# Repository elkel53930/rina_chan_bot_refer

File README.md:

**3DCADデータはこちら https://a360.co/3BOVUqo**

このリポジトリは璃奈ちゃんbotのコードの一部を参考のために公開するものです。

これらのコードは十分に整理されたものではありません。
また、あくまで参考のためのコードで、動作に必要なコードが全て揃っている保証もありません。

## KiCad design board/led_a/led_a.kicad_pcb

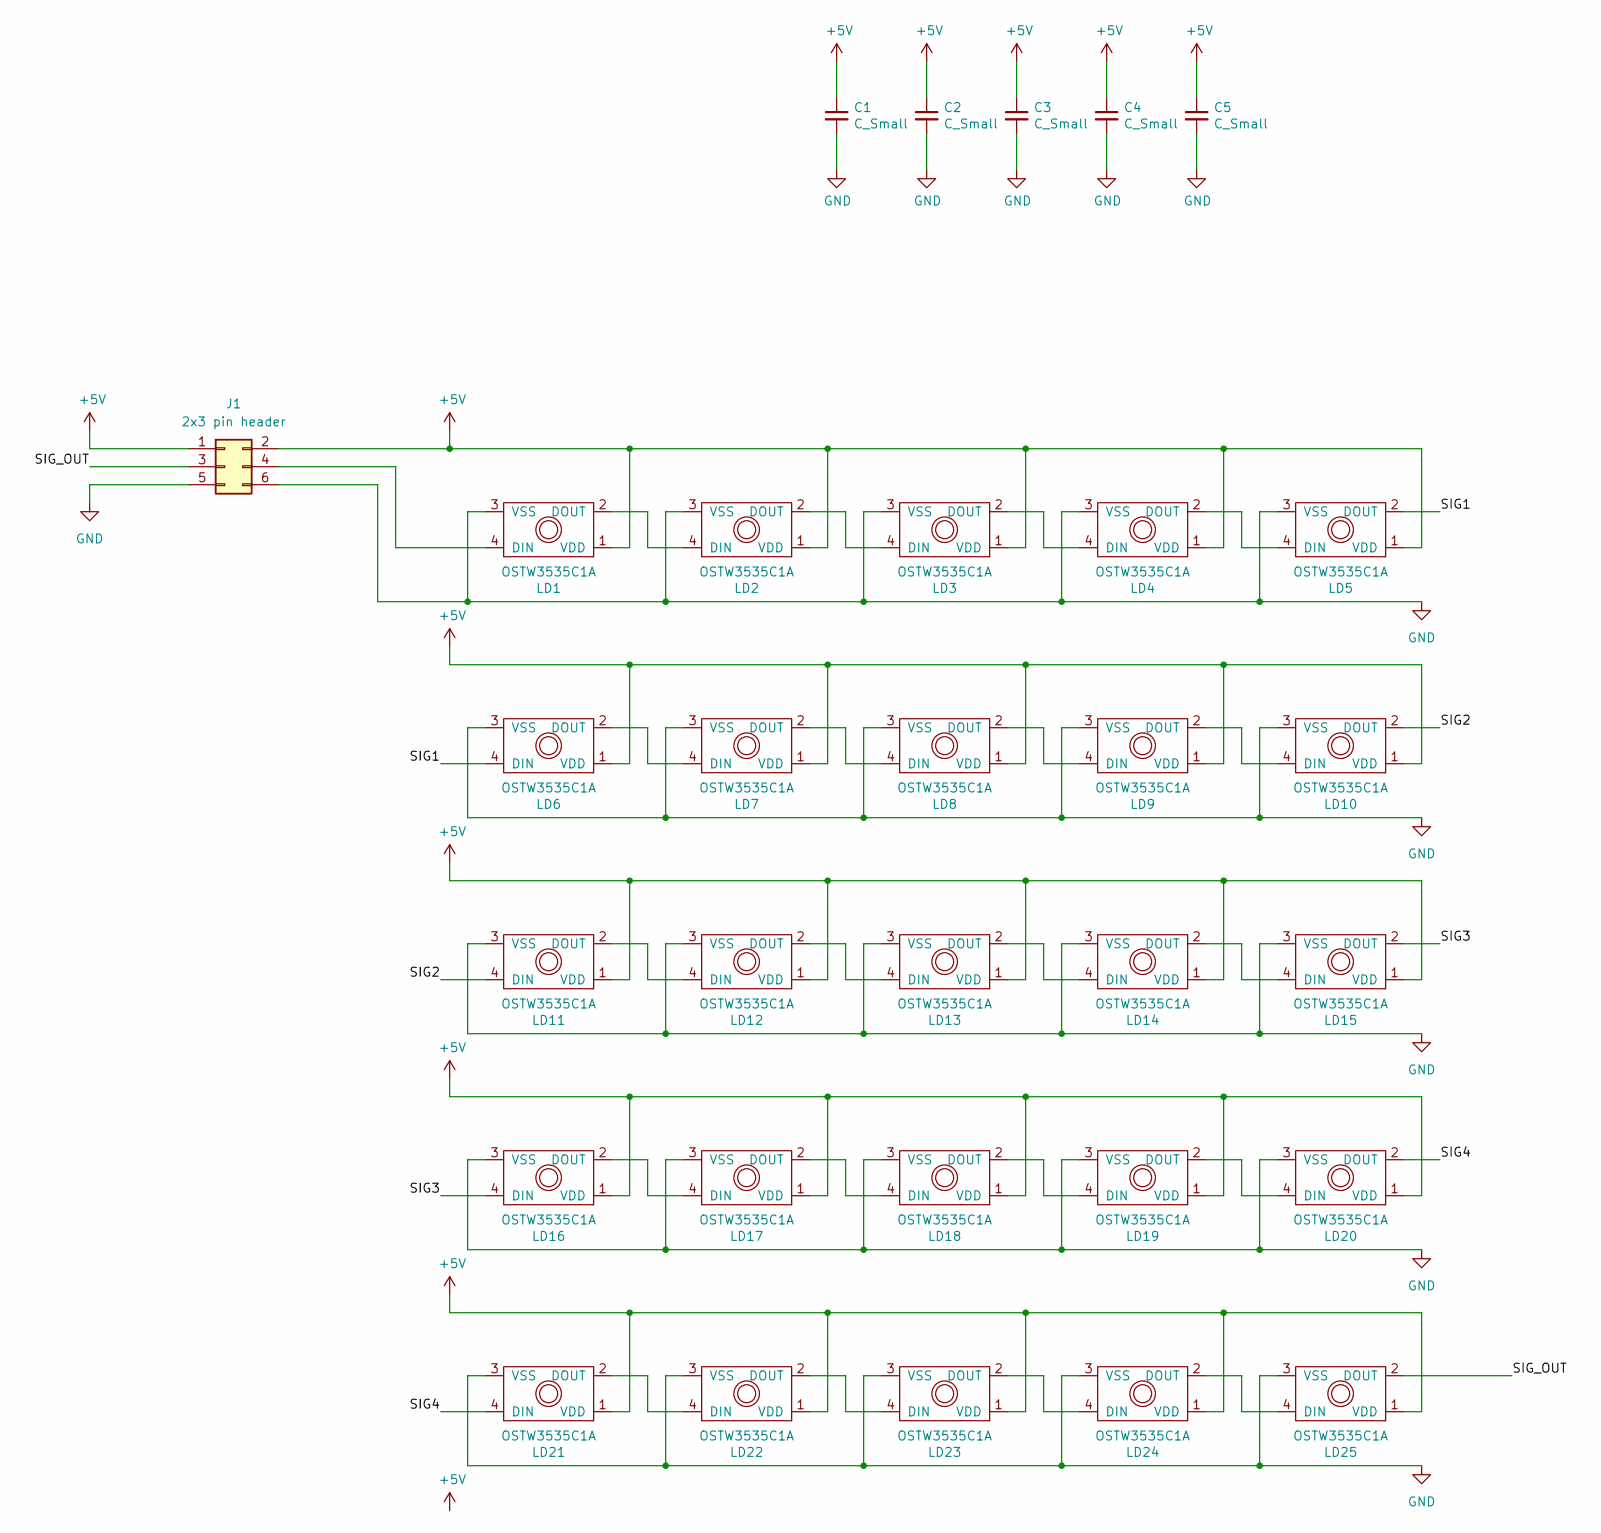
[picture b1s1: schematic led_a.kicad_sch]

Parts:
C1, C2, C3, C4, C5: C_Small; C_1206_3216Metric_Pad1.33x1.80mm_HandSolder
J1: 2x3 pin header; PinHeader_2x03_P2.54mm_Vertical
LD1, LD2, LD3, LD4, LD5, LD6, LD7, LD8, LD9, LD10, LD11, LD12, LD13, LD14, LD15, LD16, LD17, LD18, LD19, LD20, LD21, LD22, LD23, LD24, LD25: OSTW3535C1A

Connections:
+5V: C1.1, C2.1, C3.1, C4.1, C5.1, J1.1, J1.2, LD1.1 (VDD), LD2.1 (VDD), LD3.1 (VDD), LD4.1 (VDD), LD5.1 (VDD), LD6.1 (VDD), LD7.1 (VDD), LD8.1 (VDD), LD9.1 (VDD), LD10.1 (VDD), LD11.1 (VDD), LD12.1 (VDD), LD13.1 (VDD), LD14.1 (VDD), LD15.1 (VDD), LD16.1 (VDD), LD17.1 (VDD), LD18.1 (VDD), LD19.1 (VDD), LD20.1 (VDD), LD21.1 (VDD), LD22.1 (VDD), LD23.1 (VDD), LD24.1 (VDD), LD25.1 (VDD)
/SIG1: LD5.2 (DOUT), LD6.4 (DIN)
/SIG2: LD10.2 (DOUT), LD11.4 (DIN)
/SIG3: LD15.2 (DOUT), LD16.4 (DIN)
/SIG4: LD20.2 (DOUT), LD21.4 (DIN)
/SIG_OUT: J1.3, LD25.2 (DOUT)
GND: C1.2, C2.2, C3.2, C4.2, C5.2, J1.5, J1.6, LD1.3 (VSS), LD2.3 (VSS), LD3.3 (VSS), LD4.3 (VSS), LD5.3 (VSS), LD6.3 (VSS), LD7.3 (VSS), LD8.3 (VSS), LD9.3 (VSS), LD10.3 (VSS), LD11.3 (VSS), LD12.3 (VSS), LD13.3 (VSS), LD14.3 (VSS), LD15.3 (VSS), LD16.3 (VSS), LD17.3 (VSS), LD18.3 (VSS), LD19.3 (VSS), LD20.3 (VSS), LD21.3 (VSS), LD22.3 (VSS), LD23.3 (VSS), LD24.3 (VSS), LD25.3 (VSS)
unnamed: LD1.2 (DOUT), LD2.4 (DIN)
unnamed: J1.4, LD1.4 (DIN)
unnamed: LD2.2 (DOUT), LD3.4 (DIN)
unnamed: LD3.2 (DOUT), LD4.4 (DIN)
unnamed: LD4.2 (DOUT), LD5.4 (DIN)
unnamed: LD6.2 (DOUT), LD7.4 (DIN)
unnamed: LD7.2 (DOUT), LD8.4 (DIN)
unnamed: LD8.2 (DOUT), LD9.4 (DIN)
unnamed: LD9.2 (DOUT), LD10.4 (DIN)
unnamed: LD11.2 (DOUT), LD12.4 (DIN)
unnamed: LD12.2 (DOUT), LD13.4 (DIN)
unnamed: LD13.2 (DOUT), LD14.4 (DIN)
unnamed: LD14.2 (DOUT), LD15.4 (DIN)
unnamed: LD16.2 (DOUT), LD17.4 (DIN)
unnamed: LD17.2 (DOUT), LD18.4 (DIN)
unnamed: LD18.2 (DOUT), LD19.4 (DIN)
unnamed: LD19.2 (DOUT), LD20.4 (DIN)
unnamed: LD21.2 (DOUT), LD22.4 (DIN)
unnamed: LD22.2 (DOUT), LD23.4 (DIN)
unnamed: LD23.2 (DOUT), LD24.4 (DIN)
unnamed: LD24.2 (DOUT), LD25.4 (DIN)

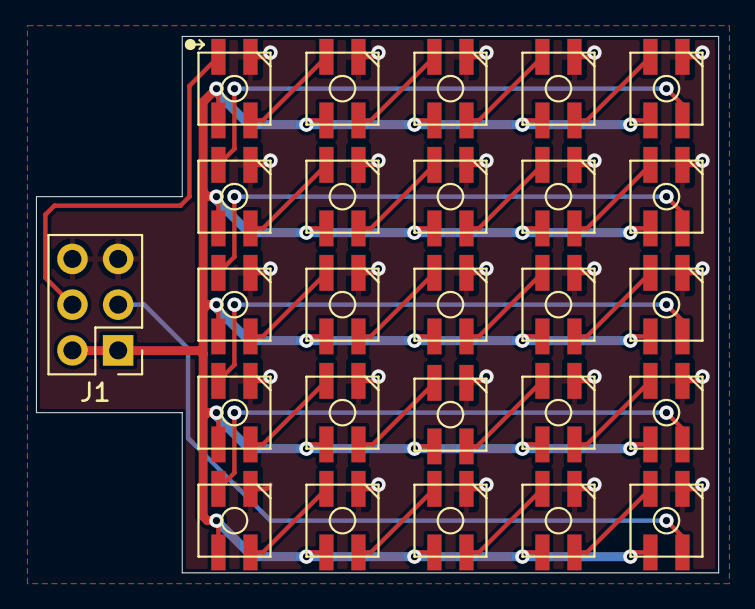
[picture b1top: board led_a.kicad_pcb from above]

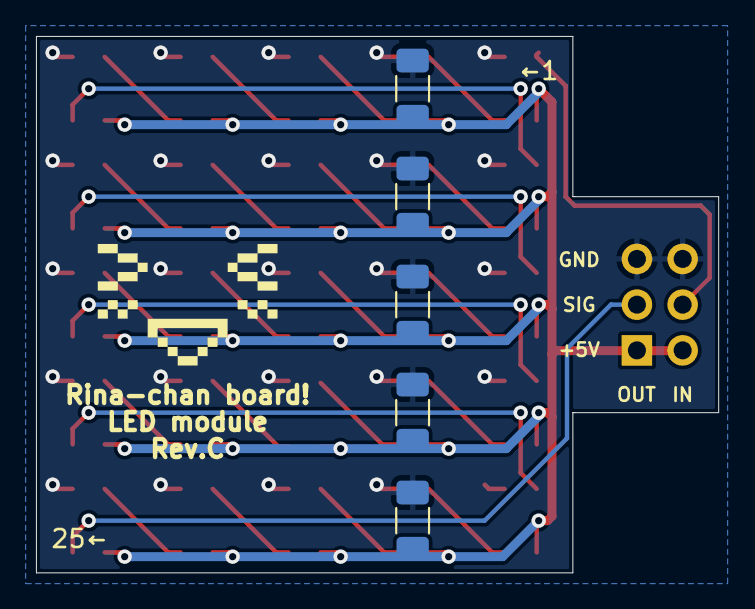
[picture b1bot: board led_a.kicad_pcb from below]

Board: 2 copper layers, 37.9 x 29.8 mm, 31 parts (5 on the bottom side), 28 nets.

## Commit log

2024-12-30 add the link to the 3D CAD data
